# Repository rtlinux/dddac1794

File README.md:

# dddac1794
Eagle PCB files for the [DDDAC1794](http://www.dddac.com/dddac1794.html).

The motherboard designed by Doede Douma is very large and uses excessive amounts of space.

My design was made in order to keep the cost of the PCBs down and make it easier to produce the PCBs by hand.

## I2S Data Shifter

[OSH Park project](https://oshpark.com/shared_projects/d8tB1U43).

[Mouser project](http://www.mouser.com/ProjectManager/ProjectDetail.aspx?AccessID=fa918c21fc).

### BOM

- C1-C6: Vishay 100nF 63V
- C7: Nichicon KZ Muse 470uF 25V
- C8: Nichicon KZ Muse 47uF 25V
- IT1: ST LF33CV
- IC1-IC5: Fairchild 74VHC164MX

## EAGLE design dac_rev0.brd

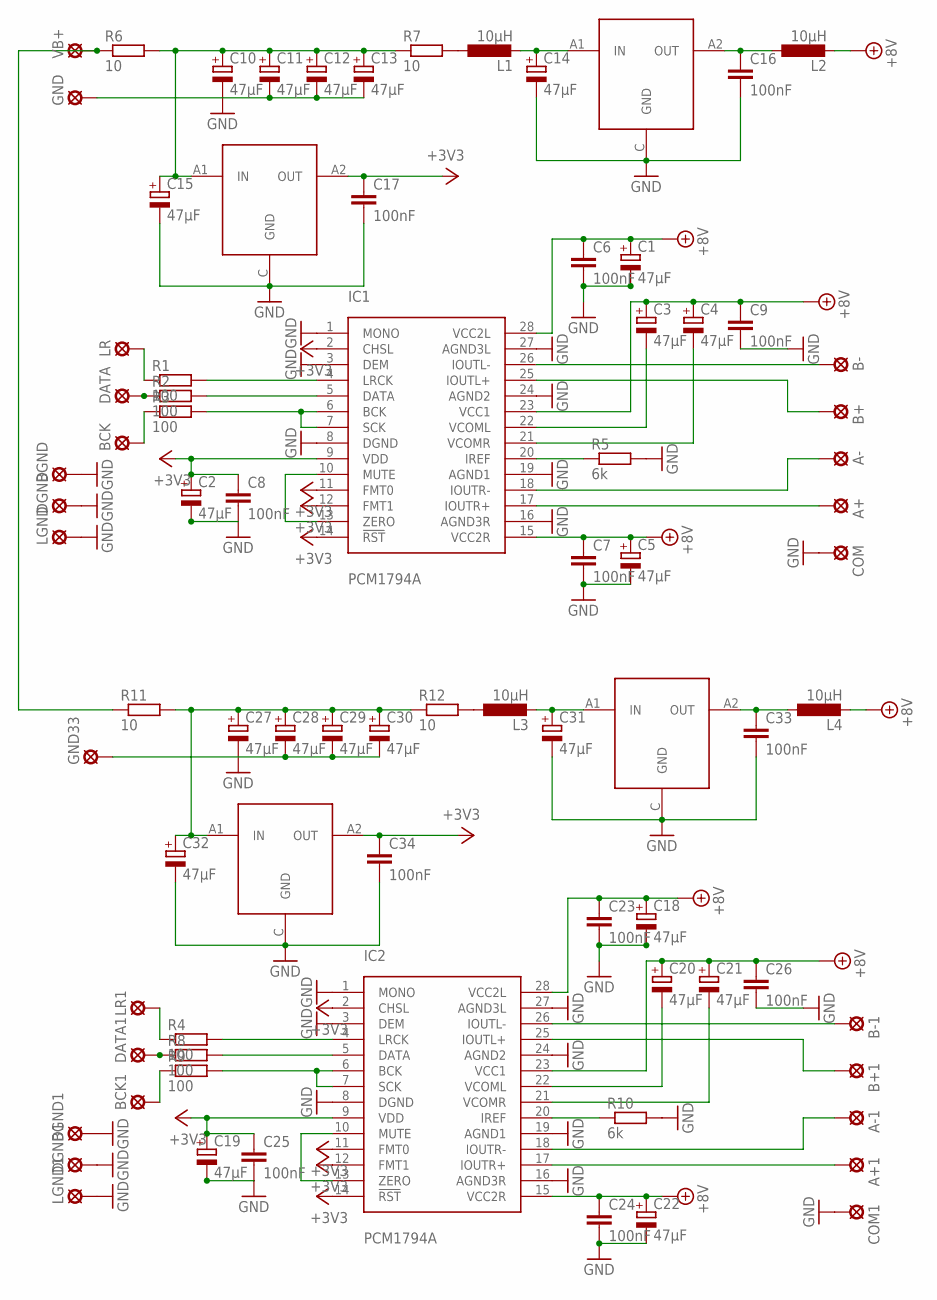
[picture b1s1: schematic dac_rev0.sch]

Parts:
A+, A+1: LSP10
A-, A-1: LSP10
B+, B+1: LSP10
B-, B-1: LSP10
BCK, BCK1: LSP10
BGND, BGND1: LSP10
C1, C2, C3, C4, C5, C10, C11, C12, C13, C14, C15, C18, C19, C20, C21, C22, C27, C28, C29, C30, C31, C32: 47µF; E5-10,5
C6, C7, C8, C9, C16, C17, C23, C24, C25, C26, C33, C34: 100nF; C050-025X075
COM, COM1: LSP10
DATA, DATA1: LSP10
DGND, DGND1: LSP10
GND, GND33: LSP10
IC1, IC2: PCM1794A; SSOP28
L1, L2, L3, L4: 10μH; 0207/10
LF1, LF33: LF33ABDT-TR; DPACK_3
LF2, LF80: LF80ABDT-TR; DPACK_3
LGND, LGND1: LSP10
LR, LR1: LSP10
R1, R2, R3, R4, R8, R9: 100; 0204/5
R5, R10: 6k; 0204/5
R6, R7, R11, R12: 10; 0204/7
VB+: LSP10

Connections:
+3V3: C2.+, C8.1, C17.1, C19.+, C25.1, C34.1, IC1.2 (CHSL), IC1.9 (VDD), IC1.11 (FMT0), IC1.12 (FMT1), IC1.14 (!RST), IC2.2 (CHSL), IC2.9 (VDD), IC2.11 (FMT0), IC2.12 (FMT1), IC2.14 (!RST), LF1.A2 (OUT), LF33.A2 (OUT)
+8V: C1.+, C3.+, C4.+, C5.+, C6.1, C7.1, C9.1, C18.+, C20.+, C21.+, C22.+, C23.1, C24.1, C26.1, IC1.15 (VCC2R), IC1.23 (VCC1), IC1.28 (VCC2L), IC2.15 (VCC2R), IC2.23 (VCC1), IC2.28 (VCC2L), L2.2, L4.2
GND: BGND.MP, BGND1.MP, C1.-, C2.-, C5.-, C6.2, C7.2, C8.2, C9.2, C10.-, C11.-, C12.-, C13.-, C14.-, C15.-, C16.2, C17.2, C18.-, C19.-, C22.-, C23.2, C24.2, C25.2, C26.2, C27.-, C28.-, C29.-, C30.-, C31.-, C32.-, C33.2, C34.2, COM.MP, COM1.MP, DGND.MP, DGND1.MP, GND.MP, GND33.MP, IC1.1 (MONO), IC1.3 (DEM), IC1.8 (DGND), IC1.16 (AGND3R), IC1.19 (AGND1), IC1.24 (AGND2), IC1.27 (AGND3L), IC2.1 (MONO), IC2.3 (DEM), IC2.8 (DGND), IC2.16 (AGND3R), IC2.19 (AGND1), IC2.24 (AGND2), IC2.27 (AGND3L), LF1.C (GND), LF2.C (GND), LF33.C (GND), LF80.C (GND), LGND.MP, LGND1.MP, R5.2, R10.2
unnamed: IC1.10 (MUTE), IC1.13 (ZERO)
unnamed: BCK.MP, R3.1
unnamed: DATA.MP, R2.1
unnamed: IC1.4 (LRCK), R1.2
unnamed: IC1.6 (BCK), IC1.7 (SCK), R3.2
unnamed: IC1.20 (IREF), R5.1
unnamed: LR.MP, R1.1
unnamed: IC1.5 (DATA), R2.2
unnamed: B-.MP, IC1.26 (IOUTL-)
unnamed: B+.MP, IC1.25 (IOUTL+)
unnamed: A-.MP, IC1.18 (IOUTR-)
unnamed: A+.MP, IC1.17 (IOUTR+)
unnamed: C3.-, IC1.22 (VCOML)
unnamed: C4.-, IC1.21 (VCOMR)
unnamed: C10.+, C11.+, C12.+, C13.+, C15.+, LF33.A1 (IN), R6.2, R7.1
unnamed: L1.1, R7.2
unnamed: IC2.10 (MUTE), IC2.13 (ZERO)
unnamed: C14.+, L1.2, LF80.A1 (IN)
unnamed: DATA1.MP, R8.1
unnamed: IC2.4 (LRCK), R4.2
unnamed: C16.1, L2.1, LF80.A2 (OUT)
unnamed: IC2.6 (BCK), IC2.7 (SCK), R9.2
unnamed: IC2.20 (IREF), R10.1
unnamed: LR1.MP, R4.1
unnamed: B-1.MP, IC2.26 (IOUTL-)
unnamed: B+1.MP, IC2.25 (IOUTL+)
unnamed: A-1.MP, IC2.18 (IOUTR-)
unnamed: A+1.MP, IC2.17 (IOUTR+)
unnamed: C20.-, IC2.22 (VCOML)
unnamed: C21.-, IC2.21 (VCOMR)
unnamed: C27.+, C28.+, C29.+, C30.+, C32.+, LF1.A1 (IN), R11.2, R12.1
unnamed: C31.+, L3.2, LF2.A1 (IN)
unnamed: C33.1, L4.1, LF2.A2 (OUT)
unnamed: R6.1, R11.1, VB+.MP
unnamed: L3.1, R12.2
unnamed: BCK1.MP, R9.1
unnamed: IC2.5 (DATA), R8.2

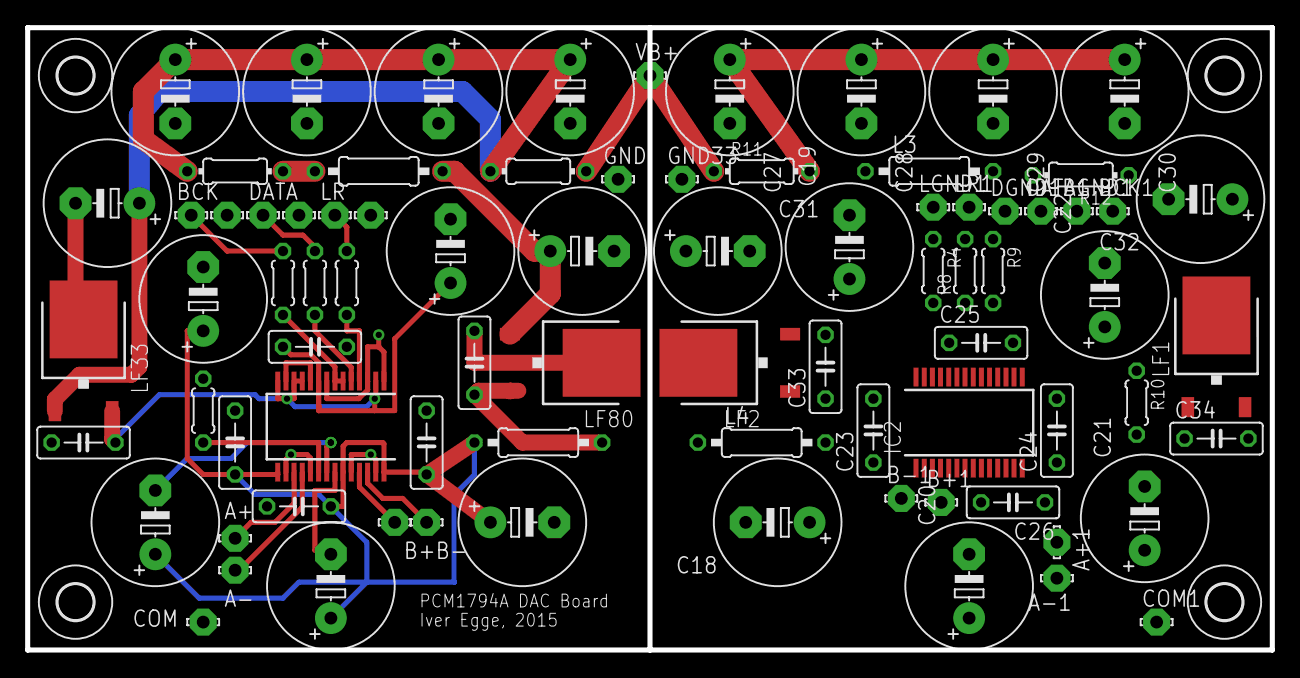
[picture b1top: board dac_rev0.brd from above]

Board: 2 copper layers, 99.1 x 49.5 mm, 85 parts (0 on the bottom side), 40 nets.

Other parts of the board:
U$3, U$4, U$5, U$6: 2,8

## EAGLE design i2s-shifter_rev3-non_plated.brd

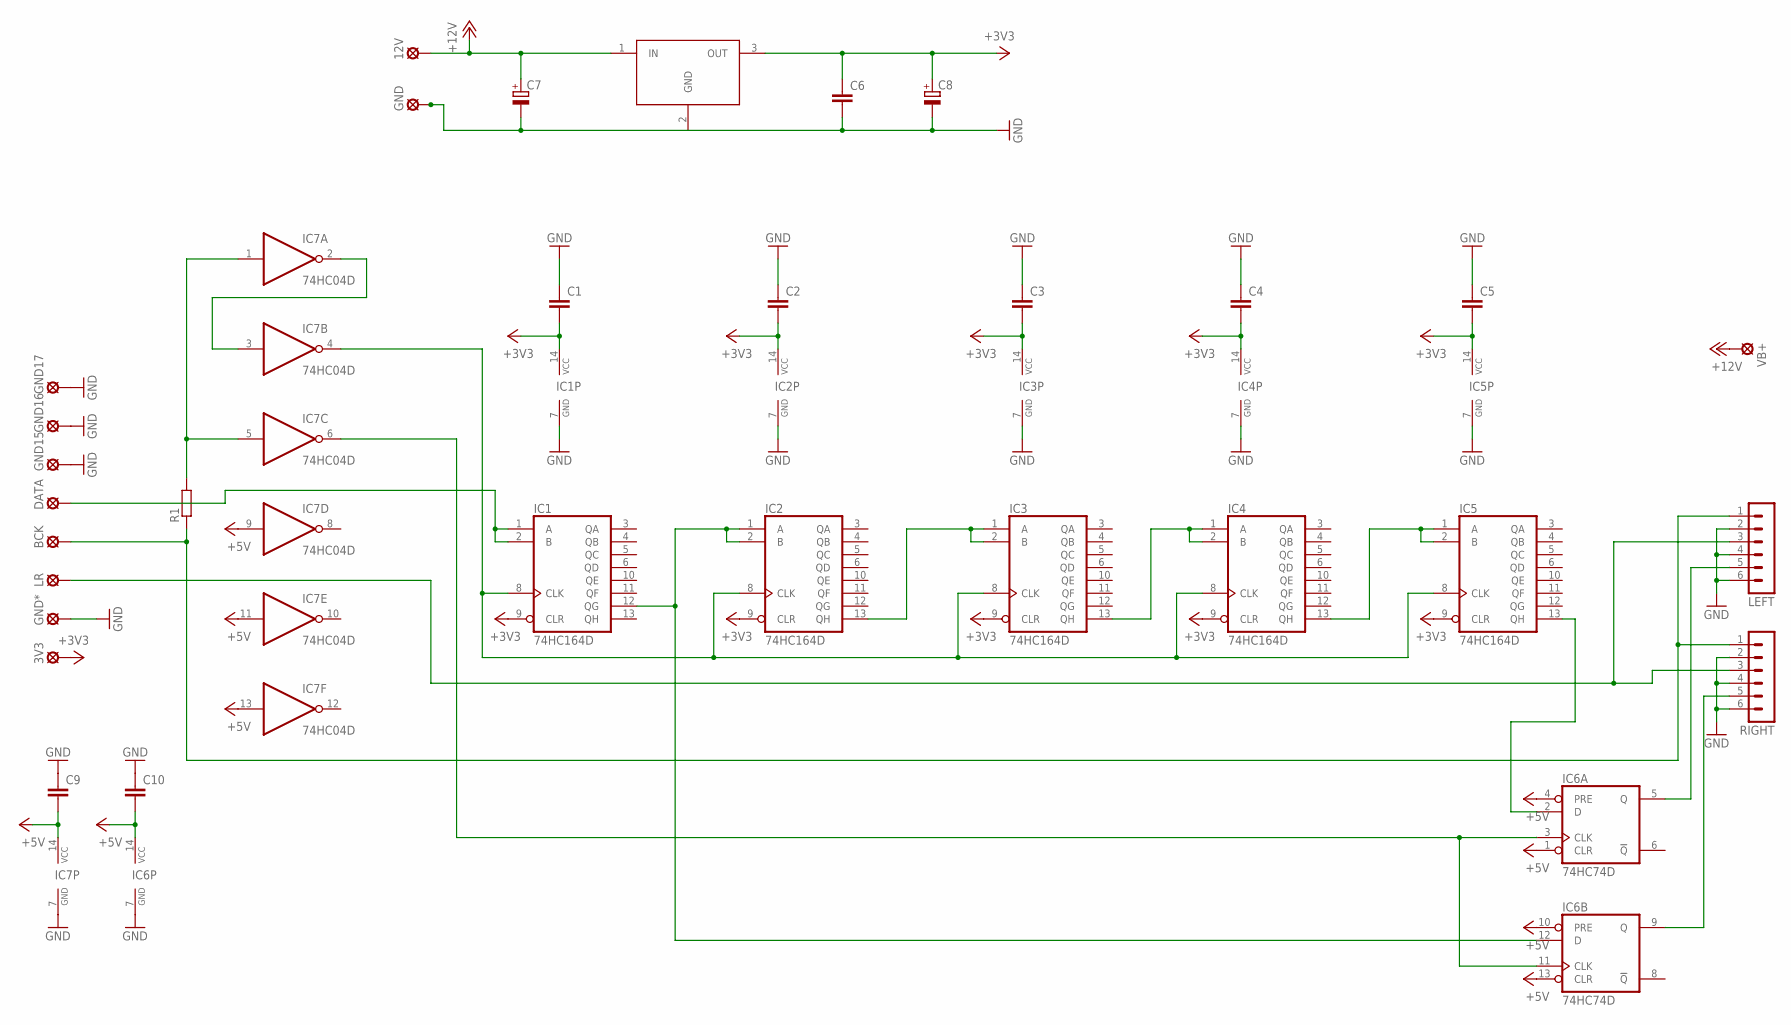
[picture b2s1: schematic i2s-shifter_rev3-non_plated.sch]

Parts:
3V3, 12V: LSP10
BCK: LSP10
C1, C2, C3, C4, C5, C6, C9, C10: C-EU050-025X075; C050-025X075
C7: CPOL-EUE7.5-16; E7,5-16
C8: CPOL-EUE5-10.5; E5-10,5
DATA: LSP10
GND, GND15, GND16, GND17: LSP10
GND*: LSP10
IC1, IC2, IC3, IC4, IC5: 74HC164D; SO14
IC6: 74HC74D; SO14
IC7: 74HC04D; SO14
IT1: LM3940IT-3.3; TO220V
LEFT: MA06-1
LR: LSP10
R1: R-EU_0204/5; 0204/5
RIGHT: MA06-1
VB+: LSP10

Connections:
+3V3: 3V3.MP, C1.2, C2.2, C3.2, C4.2, C5.2, C6.1, C8.+, IC1.9 (CLR), IC1.14 (VCC), IC2.9 (CLR), IC2.14 (VCC), IC3.9 (CLR), IC3.14 (VCC), IC4.9 (CLR), IC4.14 (VCC), IC5.9 (CLR), IC5.14 (VCC), IT1.3 (OUT)
+5V: C9.2, C10.2, IC6.1 (CLR), IC6.4 (PRE), IC6.10 (PRE), IC6.13 (CLR), IC6.14 (VCC), IC7.9 (I), IC7.11 (I), IC7.13 (I), IC7.14 (VCC)
+12V: 12V.MP, C7.+, IT1.1 (IN), VB+.MP
GND: C1.1, C2.1, C3.1, C4.1, C5.1, C6.2, C7.-, C8.-, C9.1, C10.1, GND.MP, GND15.MP, GND16.MP, GND17.MP, GND*.MP, IC1.7 (GND), IC2.7 (GND), IC3.7 (GND), IC4.7 (GND), IC5.7 (GND), IC6.7 (GND), IC7.7 (GND), IT1.2 (GND), LEFT.2, LEFT.4, LEFT.6, RIGHT.2, RIGHT.4, RIGHT.6
unnamed: DATA.MP, IC1.1 (A), IC1.2 (B)
unnamed: IC1.8 (CLK), IC2.8 (CLK), IC3.8 (CLK), IC4.8 (CLK), IC5.8 (CLK), IC7.4 (O)
unnamed: IC5.13 (QH), IC6.2 (D)
unnamed: IC2.13 (QH), IC3.1 (A), IC3.2 (B)
unnamed: IC3.13 (QH), IC4.1 (A), IC4.2 (B)
unnamed: IC4.13 (QH), IC5.1 (A), IC5.2 (B)
unnamed: IC6.5 (Q), LEFT.5
unnamed: IC6.9 (Q), RIGHT.5
unnamed: LEFT.3, LR.MP, RIGHT.3
unnamed: BCK.MP, LEFT.1, R1.1, RIGHT.1
unnamed: IC7.2 (O), IC7.3 (I)
unnamed: IC6.3 (CLK), IC6.11 (CLK), IC7.6 (O)
unnamed: IC1.12 (QG), IC2.1 (A), IC2.2 (B), IC6.12 (D)
unnamed: IC7.1 (I), IC7.5 (I), R1.2

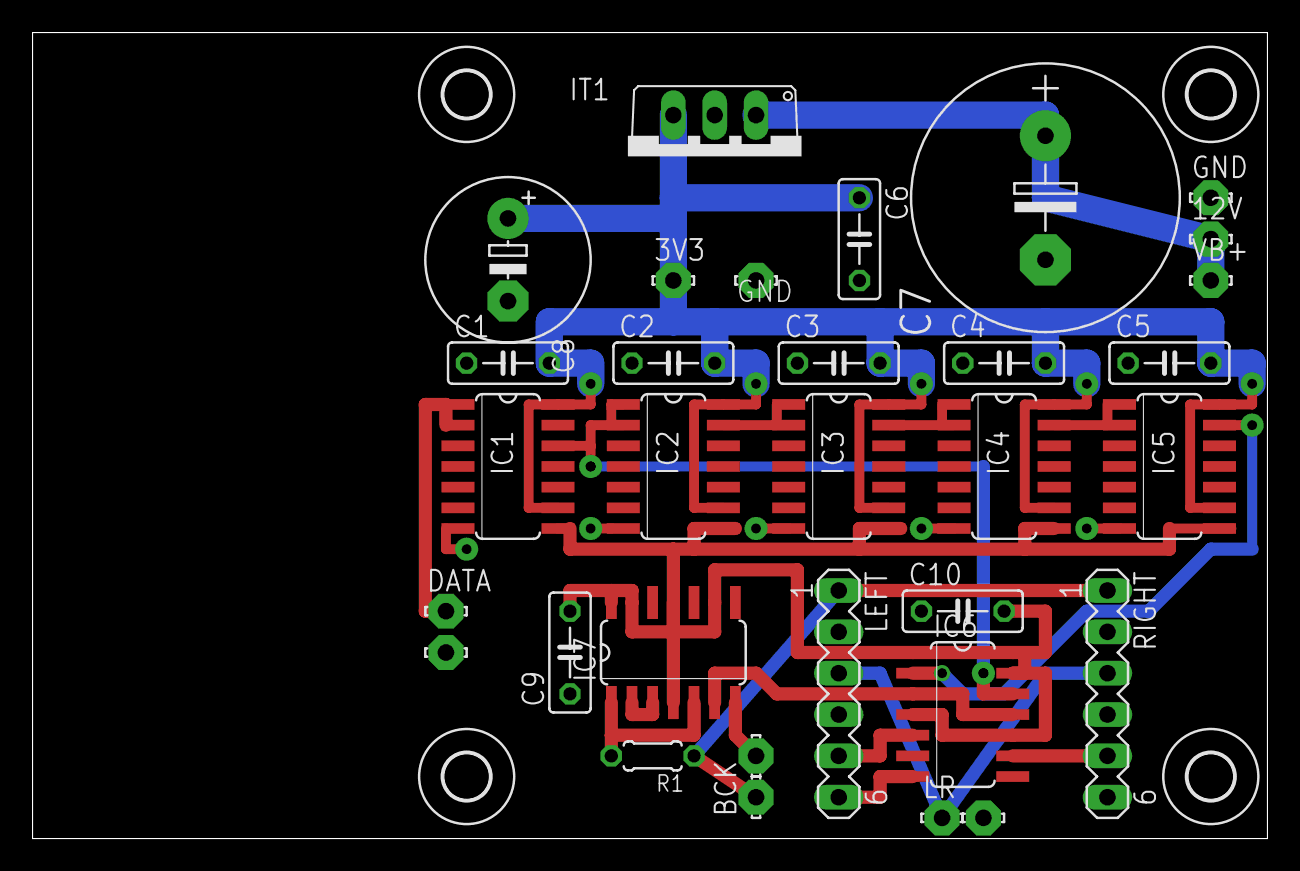
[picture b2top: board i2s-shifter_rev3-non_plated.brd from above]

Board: 2 copper layers, 75.9 x 49.5 mm, 36 parts (0 on the bottom side), 18 nets.

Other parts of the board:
U$1, U$2, U$3, U$4: 2,8

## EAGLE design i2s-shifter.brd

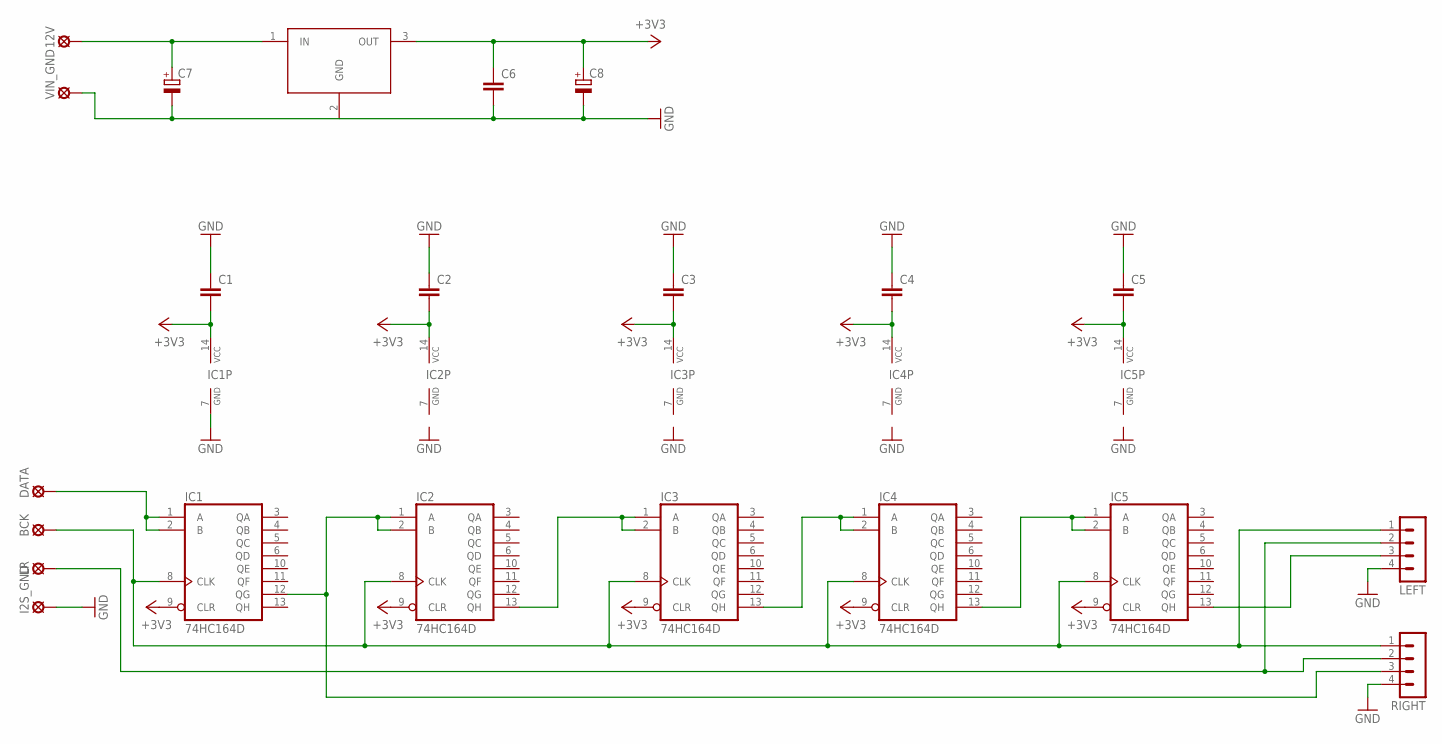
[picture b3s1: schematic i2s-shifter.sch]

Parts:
12V: LSP10
BCK: LSP10
C1, C2, C3, C4, C5, C6: C-EU050-025X075; C050-025X075
C7: CPOL-EUE7.5-16; E7,5-16
C8: CPOL-EUE5-10.5; E5-10,5
DATA: LSP10
I2S_GND: LSP10
IC1, IC2, IC3, IC4, IC5: 74HC164D; SO14
IT1: LM3940IT-3.3; TO220V
LEFT: MA04-1
LR: LSP10
RIGHT: MA04-1
VIN_GND: LSP10

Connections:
+3V3: C1.2, C2.2, C3.2, C4.2, C5.2, C6.1, C8.+, IC1.9 (CLR), IC1.14 (VCC), IC2.9 (CLR), IC2.14 (VCC), IC3.9 (CLR), IC3.14 (VCC), IC4.9 (CLR), IC4.14 (VCC), IC5.9 (CLR), IC5.14 (VCC), IT1.3 (OUT)
unnamed: DATA.MP, IC1.1 (A), IC1.2 (B)
unnamed: BCK.MP, IC1.8 (CLK), IC2.8 (CLK), IC3.8 (CLK), IC4.8 (CLK), IC5.8 (CLK), LEFT.1, RIGHT.1
unnamed: IC1.12 (QG), IC2.1 (A), IC2.2 (B), RIGHT.3
unnamed: IC2.13 (QH), IC3.1 (A), IC3.2 (B)
unnamed: IC3.13 (QH), IC4.1 (A), IC4.2 (B)
unnamed: IC4.13 (QH), IC5.1 (A), IC5.2 (B)
unnamed: LEFT.2, LR.MP, RIGHT.2
unnamed: IC5.13 (QH), LEFT.3
unnamed: 12V.MP, C7.+, IT1.1 (IN)
NS999: C1.1, C2.1, C3.1, C4.1, C5.1, C6.2, C7.-, C8.-, I2S_GND.MP, IC1.7 (GND), IC2.7 (GND), IC3.7 (GND), IC4.7 (GND), IC5.7 (GND), IT1.2 (GND), LEFT.4, RIGHT.4, VIN_GND.MP

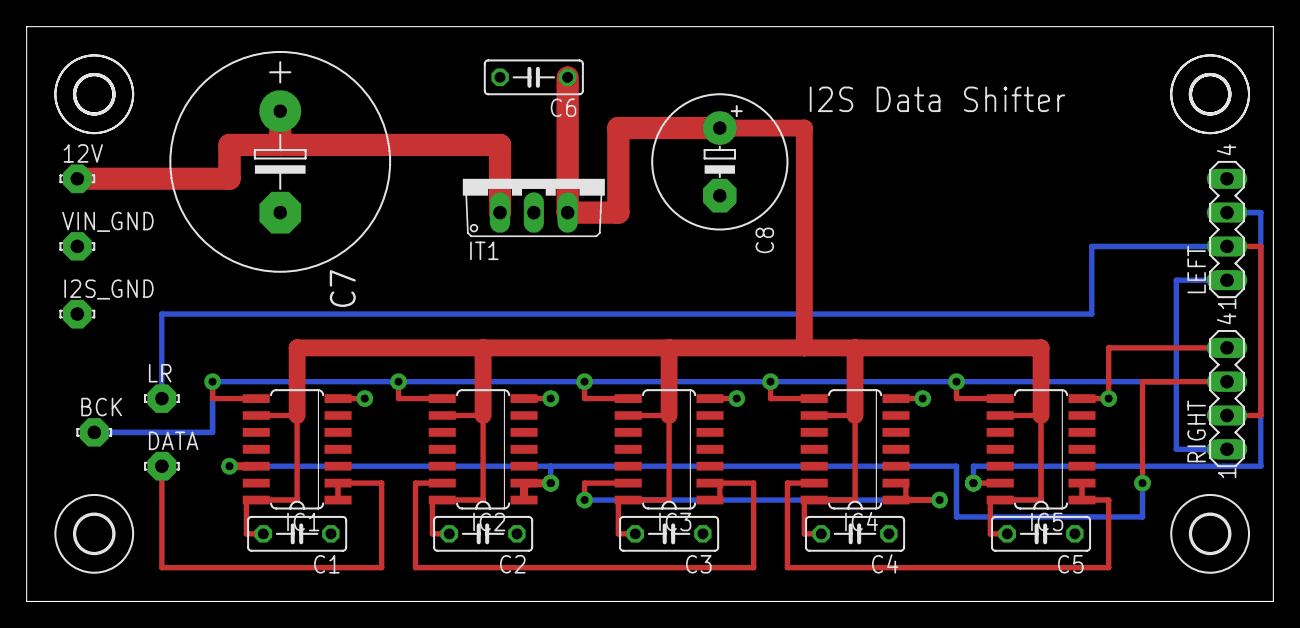
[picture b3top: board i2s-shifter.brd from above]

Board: 2 copper layers, 93.7 x 43.2 mm, 28 parts (0 on the bottom side), 11 nets.

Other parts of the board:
U$1, U$2, U$3, U$4, U$5, U$6: 2,8

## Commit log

2015-06-06 i2s shifter board
2015-06-07 moved caps closer to vcc
2015-06-07 rev1. much better arrangment of components. shorter signal paths
2015-06-07 rev2. made board smaller than 100x50mm
2015-06-08 through hole components soldered only on bottom layer. ground pads for twisted wiring
2015-06-10 rev3
2015-06-14 wip dac board. added libs
2015-06-14 minor tweak
2019-07-14 continue WIP for dac rev0
